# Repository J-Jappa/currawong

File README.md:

# Currawong

A pocket music player with a haptic dial. Streams Spotify, plays local FLAC, and outputs to wired headphones through a USB DAC or to Bluetooth headphones. A Raspberry Pi Zero W runs the audio and UI on a 1-bit Sharp memory LCD, and an ESP32-S3 drives a brushless motor as a software-defined dial.

## Why

Currawong started, and remains, a gift. I started about three weeks before it was due, so time pressure was high, especially fitting it around work. I listen to a lot of music, and it brings me a lot of joy. One thing that feels increasingly problematic is the lack of intentionality in what we listen to and how we support artists. On top of this, I'm an increasing fan of the idea that something doesn't have to do everything, and that the friction between things leads to more intentionality. Hence the desire to build a dedicated music player, and a high-quality one at that.

That being said, as Currawong is a gift, I did want versatility in this approach. The end goal is a device that can be used day to day with limited compromises, and one that is built with care and attention. Hopefully this means it can bring a little bit of joy every day. Because of that, Currawong supports both Spotify and offline FLAC/MP3 playback, with the weighting on offline functionality. It also supports wired and Bluetooth audio devices, again with more weight on the wired approach.

## Features

**Playback**
- Spotify Connect receiver via [go-librespot](https://github.com/devgianlu/go-librespot), shown as "Currawong" in the Spotify app
- Local library (FLAC and other formats) via [MPD](https://www.musicpd.org/), with artists, albums, playlists and an Up Next queue
- Wired output through a [Moondrop Dawn Pro 2](https://www.linsoul.com/products/moondrop-dawn-pro2) USB DAC with hardware volume, or Bluetooth A2DP via [BlueALSA](https://github.com/arkq/bluez-alsa)
- Five-band equaliser on the wired output (alsaequal with [CAPS](https://wiki.linuxaudio.org/apps/all/caps) Eq10, ±6 dB per band)
- Pinned Spotify playlists, shuffle, repeat, add to playlist
- Browser upload page at `http://currawong.local` for adding music from any device on the same network

**Interface**
- 240 × 400 portrait UI on a 1-bit Sharp memory LCD, rendered event-driven: a screen is only redrawn when something on it changes, and only the changed panel lines are sent
- A simple cover, track and progress screen for Spotify. Local files add spectrum strips down the sides, and an oscilloscope page in FULL visuals (Settings > Visuals: FULL, REGULAR or FAST)
- An animated pixel currawong that sings, hops, sleeps and idles depending on playback state, plus a boot animation
- On-screen keyboard for joining Wi-Fi, Bluetooth pairing, sleep and auto-off timers, and settings for dial feel, button click strength and screen rotation

**Haptic dial**
- Voltage-mode FOC on a [DFRobot 2804](https://www.dfrobot.com/product-3005.html) gimbal motor with an AS5600 magnetic encoder, using [SimpleFOC](https://simplefoc.com)
- The UI sets the dial's feel per screen: one detent per item with end stops in menus, 48 light clicks per turn for scrubbing with walls at 0:00 and the end of the track, one click per dB on the equaliser
- Momentum coasting on long lists, stronger landmark clicks at each new letter, a magnetic pull to the playing track in Up Next
- The dial spins a full turn on track skip and rolls while auto-scrubbing, and can be pocket-locked
- Firmware updates are sent from the Pi over the existing UART link and written to the ESP32's spare OTA partition, so the dial never needs to come out of the case to be reflashed
- Haptic approach follows the open-source [SmartKnob](https://github.com/scottbez1/smartknob)

**Power**
- 5000 mAh single-cell LiPo through an Adafruit PowerBoost 1000C, with a MAX17048 fuel gauge
- Low-battery alerts on the dial at 10% and 5%, and a clean shutdown at low charge or low cell voltage
- Motor is disabled after 3 s without movement, and the ESP32 drops to 80 MHz while idle

## System

```mermaid
flowchart LR
    BAT[1S LiPo] --> GAUGE[MAX17048<br/>fuel gauge]
    GAUGE --> PB[PowerBoost 1000C<br/>charger + 5 V boost]
    USB[USB-C] --> PB
    PB -- 5 V --> PI[Raspberry Pi Zero W<br/>audio, UI]
    PB -- 5 V --> TMC[TMC6300<br/>motor driver]
    PB -- 5 V via Schottky --> ESP[XIAO ESP32-S3<br/>FOC loop]
    PI -- SPI --> LCD[Sharp 2.7in<br/>memory LCD]
    PI -- I2C --> GAUGE
    PI -- GPIO --> BTN[5 buttons]
    PI -- USB OTG --> DAC[Dawn Pro 2<br/>USB DAC] --> HP[3.5 mm out]
    PI -. Bluetooth A2DP .-> BT[Headphones]
    PI <-- UART --> ESP
    ESP -- 6 PWM --> TMC --> MOT[2804 BLDC]
    MOT --- ENC[AS5600] -- I2C --> ESP
```

| Part | Role |
| --- | --- |
| [Raspberry Pi Zero W](https://www.raspberrypi.com/products/raspberry-pi-zero-w/) | Audio (go-librespot, MPD), UI, display, buttons |
| [Seeed XIAO ESP32-S3](https://www.seeedstudio.com/XIAO-ESP32S3-p-5627.html) | Haptic dial: FOC loop, encoder, UART link to the Pi |
| [SparkFun TMC6300 breakout](https://www.sparkfun.com/sparkfun-brushless-motor-driver-3-phase-tmc6300.html) | 3-phase motor driver |
| [DFRobot 2804 motor with AS5600](https://www.dfrobot.com/product-3005.html) | Dial motor and angle sensor |
| [Adafruit Sharp 2.7" memory LCD](https://www.adafruit.com/product/4694) | 400 × 240, 1-bit, mounted portrait |
| [Moondrop Dawn Pro 2](https://www.linsoul.com/products/moondrop-dawn-pro2) | USB DAC and headphone amp |
| [Adafruit MAX17048](https://www.adafruit.com/product/5580) | Battery fuel gauge |
| [Adafruit PowerBoost 1000C](https://www.adafruit.com/product/2465) | Charger and 5 V boost |
| Custom PCB (Currawong v1.0) | Carrier for all of the above, designed in [KiCad](https://www.kicad.org/) |

Pin maps, the power budget, display protocol and firmware limits are in [docs/hardware.md](docs/hardware.md). The Pi to dial protocol is in [docs/dial-protocol.md](docs/dial-protocol.md).

## Repository layout

```
pi/                      Raspberry Pi software: UI, setup script, upload page, character assets
firmware/currawong_knob/ ESP32-S3 haptic dial firmware (PlatformIO, Arduino, SimpleFOC)
animation/               Boot animation frames and a desktop preview player
hardware/pcb/            KiCad project, custom symbols and footprints, Gerbers, 3D STEP
hardware/case/           SolidWorks sources and print-ready STL
hardware/logos/          DXF artwork for the case
docs/                    Hardware reference, dial protocol, setup guide, photos and UI renders
```

## Building one

1. **PCB:** order from the Gerbers in [hardware/pcb/fabrication](hardware/pcb/fabrication).
2. **Case:** print the STLs in [hardware/case/stl](hardware/case/stl). You'll also need:
   - 6 × M3 threaded inserts
   - 6 × M3 × 12 mm countersunk screws
   - 2 × M3 nuts
   - 2 × M3 × 8 mm socket head screws
   - 6 × M2.5 × 8 mm countersunk screws
3. **Dial firmware:** flash once over USB with PlatformIO. See [firmware/currawong_knob](firmware/currawong_knob).
4. **Pi:** flash Raspberry Pi OS Lite (32-bit), copy [pi/](pi) across and run `sudo bash currawong_setup.sh`. See [docs/setup.md](docs/setup.md).

The UI also runs on a desktop with no hardware attached. `python3 pi/currawong_ui.py --preview` renders each screen to PNG, and `python3 pi/bird_preview.py` renders the currawong's animations. Every UI image in this README was made that way.

## Design notes

Many design decisions here were compromises for the sake of delivering on time, and many were additions to bring it closer to the end goal of a little more joy.

### The dial

I saw a video a while ago on the open-source [SmartKnob](https://github.com/scottbez1/smartknob) project and thought it was an incredibly cool and satisfying input method. Later I saw it again in two of Teenage Engineering's products, in particular the [TP-7](https://teenage.engineering/products/tp-7). For me this felt like the perfect input method for Currawong. It pulls inspiration from the iconic [iPod click wheel](https://en.wikipedia.org/wiki/IPod_click_wheel), which carries an incredible amount of nostalgia and to me always felt a little like magic. The haptic dial takes it one step further by being physically responsive: something that feels unapologetically tactile. This is why it was a clear winner over a rotary encoder. While waiting for the haptic dial parts I used a rotary encoder as a placeholder, but it just wasn't right. It only truly felt like magic once the haptic dial was set up.

The feel changes with the screen. A menu gets one detent per item with walls at each end, scrubbing gets 48 light clicks per turn with walls at 0:00 and the end of the song, and the equaliser clicks once per dB. Flick through a long list and the clicks fade so it coasts, then come back as it slows. Each new letter in Artists and Albums clicks harder, and in Up Next the playing track pulls the dial in like a magnet.

### Splitting the processors

The processors were split after testing the Pi with a rotary encoder. With a single core, the Pi already struggles with responsiveness across the device. So to avoid any further impact, the ESP32 takes on polling the magnetic encoder and driving the motor itself. In the end this worked exceptionally well.

The two talk over a 115200 baud UART using checksummed, NMEA-style lines. The Pi only sends high-level commands (`CFG,list,12,3` is a 12-item menu, sitting on item 3) and gets positions back, so the FOC loop never waits on Linux. The Pi also can't reach the ESP32's boot pins, so firmware updates go over the same link: the image is sent in acknowledged chunks to the spare OTA partition, and the ESP32 only switches over once the MD5 matches. Once the dial is in the case, it never needs to come out to be reflashed.

### Living with a Pi Zero W

Unfortunately, the original intention of using a [Pi Zero 2 W](https://www.raspberrypi.com/products/raspberry-pi-zero-2-w/) had to be abandoned due to a complete shortage. Everywhere I looked there were none, or a long, long wait. I even tried alternatives like the [Orange Pi](https://en.wikipedia.org/wiki/Orange_Pi), but the prices here were astronomical. In the end I was stuck with a Raspberry Pi Zero W, which meant some things had to be cut in the name of performance. The original idea had spectrum visualisers lining the sides of Now Playing and a separate one for a full-screen mode. The goal was to push the Sharp display to its limit. Sadly this had to be mostly shelved. It still exists in the code under a UI setting but hasn't been updated since the first couple of prototypes. Maybe next time.

To keep everything else smooth on one core, go-librespot (about 35% CPU streaming at 320 kbps) runs at a higher priority than the UI, and only one player holds the DAC at a time. The UI only redraws when something on screen changes, and only sends the changed lines to the display, which takes about 50 ms for a full frame.

### The currawong

One of the key additions in achieving the goal of a little more joy was the animations. Made by hand in Pixel, they were incredibly fun to make and I think paid dividends. I'm by no means a talented visual artist, but I am proud of this little singing, dancing and sleeping currawong.

Under the hood it's a sheet of 32 × 32 sprites driven by a JSON spec of sequences, ticking at 8 fps off the clock so a late frame never makes it drift. Each frame only touches the columns the bird is in, so the panel gets a small partial update rather than a full redraw.

## What went wrong

One of the first "disaster" moments was when the first Pi was fried (well, probably just the Wi-Fi) by a stupid mistake of mine: swapping 5 V and 3.3 V. This resulted in me ordering another, before eventually figuring out it was just the SD card that had corrupted. So I was left with two working Pis, which is better than one. I would eventually need it when I did actually fry one. In a particularly painful mistake, after soldering all the components onto the PCB, I was testing a custom micro-USB to USB-C cable I'd made for the DAC when it all went wrong. The Pi started heating up like crazy and I quickly unplugged it. Following a very long desoldering process, with more destruction than I'd care to admit, I eventually got back up and running with the original Pi.

Another last-minute change was battery size. Originally I had a 2200 mAh LiPo and assumed I'd get good battery life. But after some testing it was clear it wasn't going to be enough. I debated between a 5000 mAh LiPo and a 21700 Li-ion cell, and eventually decided on the LiPo to keep it similar. This came with its own challenges, mainly packaging, and as a result Currawong grew. This led me down the path of "how do I make something big feel small?". This is easier said than done, but after some aggressive cut-ins, then a step back and some less aggressive cut-ins, then expanding the transparent front, I think that while it's still big, it's a lot more comfortable.

## What I'd change in v2

So many changes for a v2, with the luxury of lessons learnt and more time. There would have to be a decision here: stick with Spotify support or drop it. Dropping it would let me move away from the large, clunky and very slow-booting Pi Zero to something like another MCU. This would massively reduce size, decrease boot time, reduce power usage and potentially increase display responsiveness. But say I wanted to keep it, what else would I change? Well, I would switch to the Pi Zero 2 W. It's quad-core, much more modern and gives me so much more headroom. This way the visualiser ideas can come back.

As for the board, this would also change a lot. Instead of breakouts galore, these functions should be brought onto the PCB. It would allow for a cheaper result, more freedom in the design and a MUCH smaller package. One of my pet peeves is also charging speed. The PowerBoost charges at up to about 1 A, so the 5000 mAh cell takes five hours or more. Having more control over the components would allow faster charging, which is much needed. Bringing the motor driver on board would also mean its current-sense and fault pins could finally be wired up.

Again on size, the motor stack. Being by far the tallest part, integrating the magnetic encoder into the PCB and choosing a thinner motor would help a lot with the case packaging.

I'd also explore different case manufacturing methods. I'm a strong believer that most FDM printing should be kept to prototypes, and because of that this feels a bit like a prototype. A clear resin case would look great here, and if Spotify was dropped, a CNC'd aluminium back case would also look gorgeous.

## Licence

Software (everything in `pi/`, `firmware/` and `animation/`) is under the [MIT Licence](LICENSE).
Hardware designs (everything in `hardware/`) are under the [CERN Open Hardware Licence v2, Permissive](LICENSE-HARDWARE).

Built by [Jasper Japp](https://jasperjapp.com).

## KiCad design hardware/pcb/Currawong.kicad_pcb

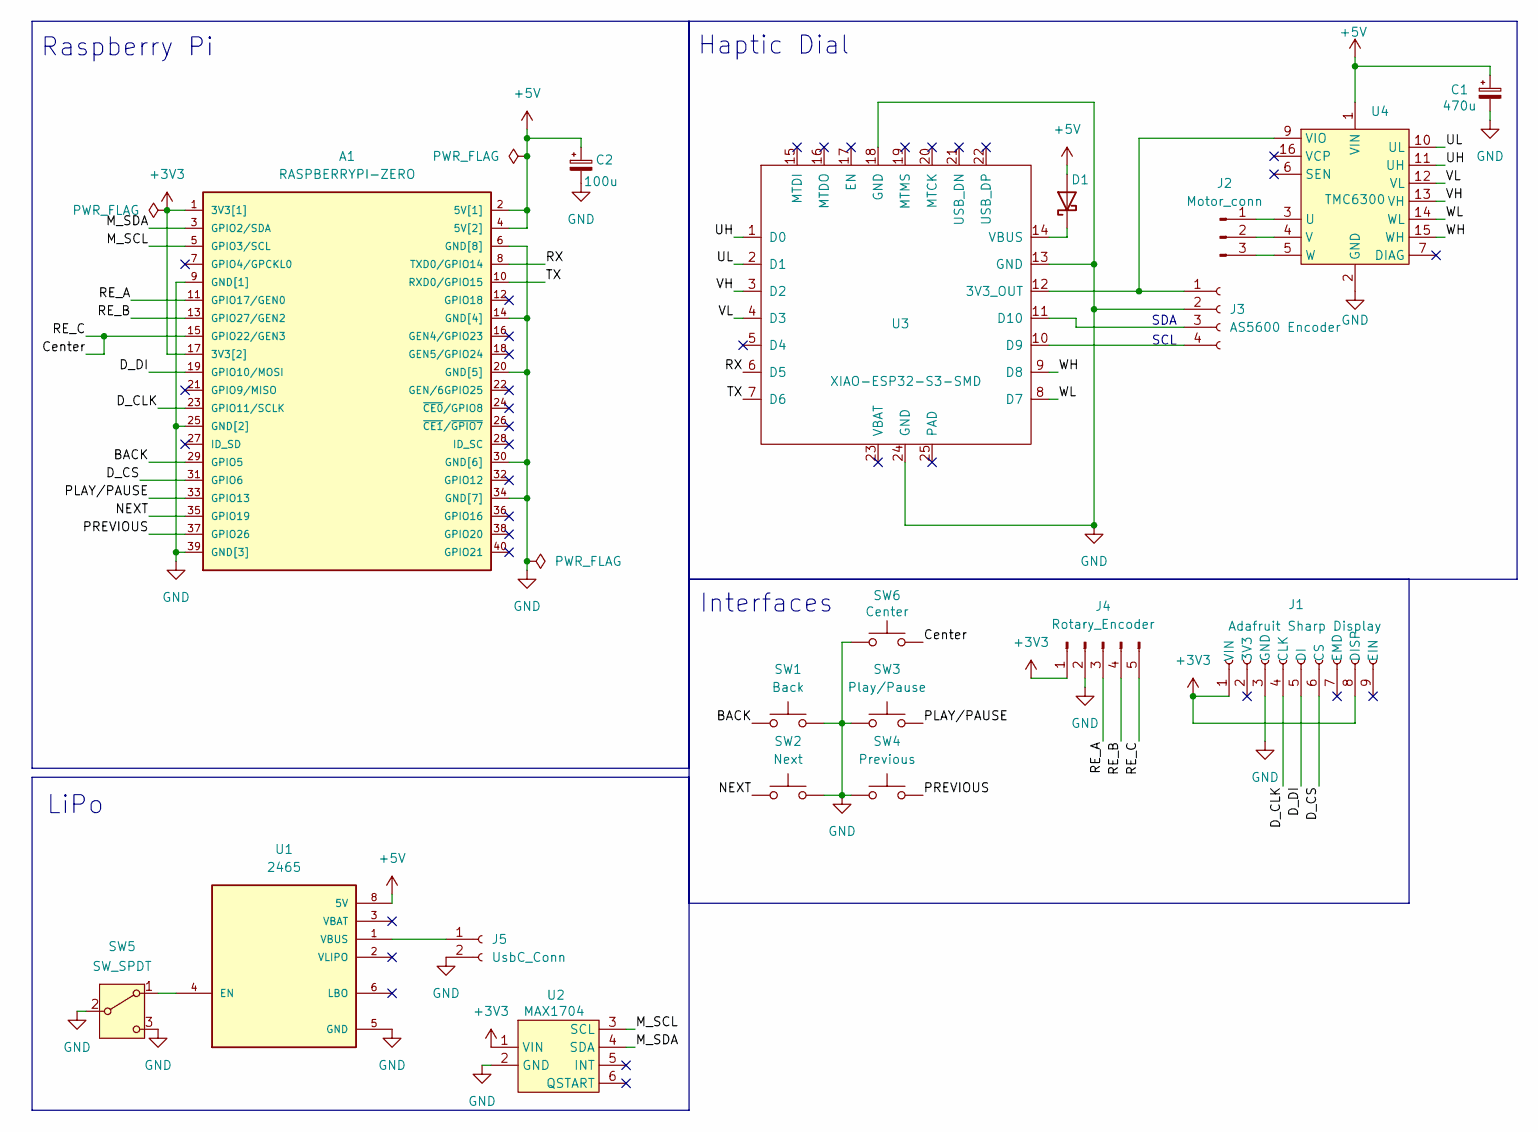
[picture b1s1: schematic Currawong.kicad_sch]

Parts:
A1: RASPBERRYPI-ZERO; RASPBERRYPI-ZERO_RPI-ZERO
C1: 470u; CP_Radial_D8.0mm_P3.50mm
C2: 100u; CP_Radial_D6.3mm_P2.50mm
D1: D_Schottky; D_DO-41_SOD81_P10.16mm_Horizontal
J1: Adafruit Sharp Display; Sharp_Display
J2: Motor_conn; JST_PH_B3B-PH-K_1x03_P2.00mm_Vertical
J3: AS5600 Encoder; JST_PH_B4B-PH-K_1x04_P2.00mm_Vertical
J4: Rotary_Encoder; JST_PH_B5B-PH-K_1x05_P2.00mm_Vertical
J5: UsbC_Conn; JST_PH_B2B-PH-K_1x02_P2.00mm_Vertical
SW1: Back; SW_PUSH_6mm_H5mm
SW2: Next; SW_PUSH_6mm_H5mm
SW3: Play/Pause; SW_PUSH_6mm_H5mm
SW4: Previous; SW_PUSH_6mm_H5mm
SW5: SW_SPDT; PinHeader_1x03_P2.54mm_Vertical
SW6: Center; SW_PUSH_6mm_H5mm
U1: 2465; MODULE_2465; PARTREV B
U2: MAX1704; AdaFruit_MAX17048
U3: XIAO-ESP32-S3-SMD
U4: TMC6300; Sparkfun_TMC6300

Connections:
+3V3: A1.1 (3V3[1]), A1.17 (3V3[2]), J1.1 (VIN), J1.8 (DISP), J4.1, U2.1 (VIN)
+5V: A1.2 (5V[1]), A1.4 (5V[2]), C1.1, C2.1, D1.2 (A), U1.8 (5V), U4.1 (VIN)
/BACK: A1.29 (GPIO5), SW1.1
/Center: A1.15 (GPIO22/GEN3), J4.5, SW6.2
/D_CLK: A1.23 (GPIO11/SCLK), J1.4 (CLK)
/D_CS: A1.31 (GPIO6), J1.6 (CS)
/D_DI: A1.19 (GPIO10/MOSI), J1.5 (DI)
/M_SCL: A1.5 (GPIO3/SCL), U2.3 (SCL)
/M_SDA: A1.3 (GPIO2/SDA), U2.4 (SDA)
/NEXT: A1.35 (GPIO19), SW2.1
/PLAY/PAUSE: A1.33 (GPIO13), SW3.2
/PREVIOUS: A1.37 (GPIO26), SW4.2
/RE_A: A1.11 (GPIO17/GEN0), J4.3
/RE_B: A1.13 (GPIO27/GEN2), J4.4
/RX: A1.8 (TXD0/GPIO14), U3.6 (D5)
/TX: A1.10 (RXD0/GPIO15), U3.7 (D6)
/UH: U3.1 (D0), U4.11 (UH)
/UL: U3.2 (D1), U4.10 (UL)
/VH: U3.3 (D2), U4.13 (VH)
/VL: U3.4 (D3), U4.12 (VL)
/WH: U3.9 (D8), U4.15 (WH)
/WL: U3.8 (D7), U4.14 (WL)
GND: A1.6 (GND[8]), A1.9 (GND[1]), A1.14 (GND[4]), A1.20 (GND[5]), A1.25 (GND[2]), A1.30 (GND[6]), A1.34 (GND[7]), A1.39 (GND[3]), C1.2, C2.2, J1.3 (GND), J3.2, J4.2, J5.2, SW1.2, SW2.2, SW3.1, SW4.1, SW5.2 (B), SW5.3 (C), SW6.1, U1.5 (GND), U1.7 (GND), U2.2 (GND), U3.13 (GND), U3.18 (GND), U3.24 (GND), U4.2 (GND), U4.8 (GND)
unnamed: D1.1 (K), U3.14 (VBUS)
unnamed: J2.1, U4.3 (U)
unnamed: J2.2, U4.4 (V)
unnamed: J2.3, U4.5 (W)
unnamed: J3.1, U3.12 (3V3_OUT), U4.9 (VIO)
unnamed: J3.3, U3.11 (D10)
unnamed: J3.4, U3.10 (D9)
unnamed: J5.1, U1.1 (VBUS)
unnamed: SW5.1 (A), U1.4 (EN)

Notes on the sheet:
LiPo
SDA
Raspberry Pi
Haptic Dial
SCL
Interfaces

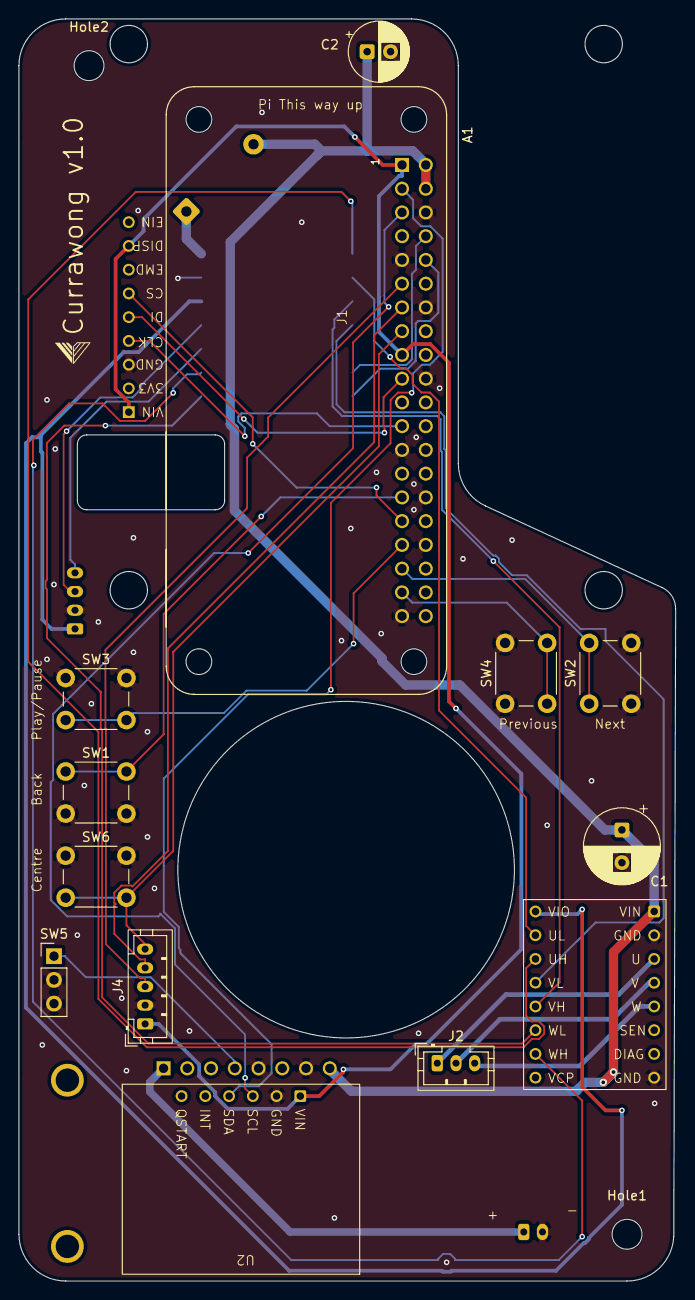
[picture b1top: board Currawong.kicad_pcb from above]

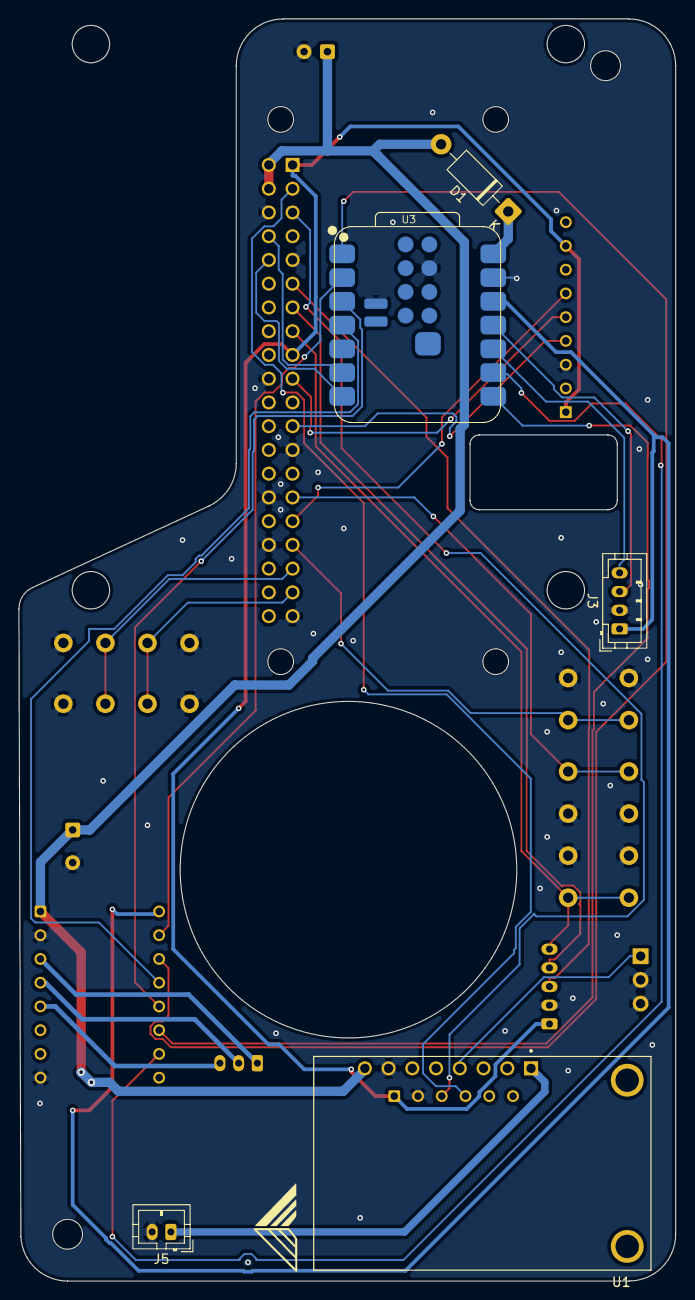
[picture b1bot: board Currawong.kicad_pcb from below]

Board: 2 copper layers, 70.2 x 135.0 mm, 23 parts (6 on the bottom side), 32 nets.

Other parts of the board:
Hole1, Hole2: MountingHole_3.2mm_M3
Logo1: LOGO; logo scaled 10mm
logo2: LOGO; logo scaled 5mm
